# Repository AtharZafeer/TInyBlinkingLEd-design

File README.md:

# TInyBlinkingLEd-design
This contains the schematic and pcb design of a circuit that will blink every 1 seconds

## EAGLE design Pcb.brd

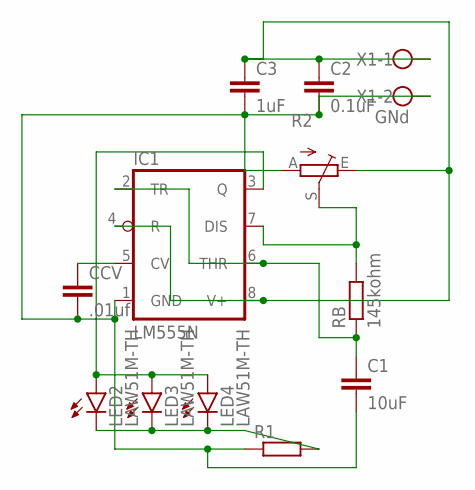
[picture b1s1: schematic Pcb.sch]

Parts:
C1: 10uF; C2.5-2
C2: 0.1uF; C025-024X044
C3: 1uF; C2.5-2
CCV: .01uf; C2.5-2
IC1: LM555N; DIL08
LED2, LED3, LED4: LAW51M-TH; W51-COOL
R1: R-EU_0309/12; 0309/12
R2: TRIM_EU-B25P; B25P
RB: 145kohm; 0309/12
X1: GNd; W237-102

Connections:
unnamed: C1.1, IC1.2 (TR), IC1.6 (THR), RB.1
unnamed: IC1.7 (DIS), R2.S, RB.2
unnamed: LED2.C, LED3.C, LED4.C, R1.2
unnamed: C1.2, C2.2, C3.2, CCV.2, IC1.1 (GND), R1.1, R2.A, X1.2
unnamed: CCV.1, IC1.5 (CV)
unnamed: C2.1, C3.1, IC1.4 (R), IC1.8 (V+), R2.E, X1.1
unnamed: IC1.3 (Q), LED2.A, LED3.A, LED4.A

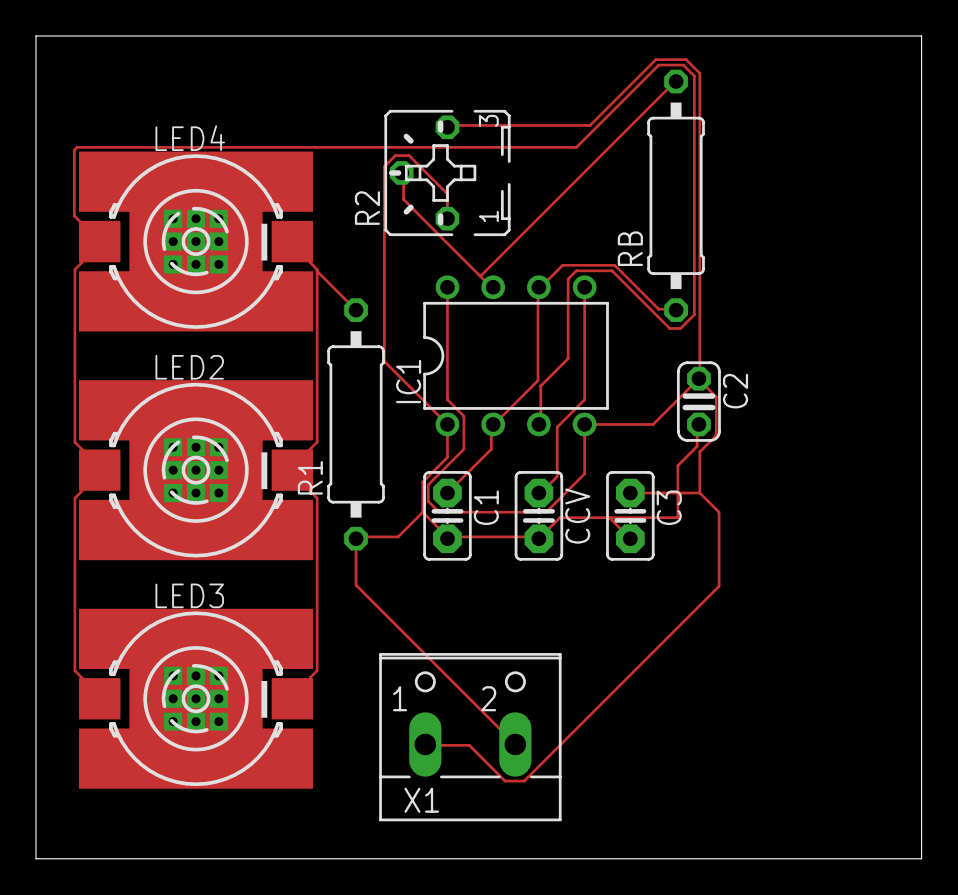
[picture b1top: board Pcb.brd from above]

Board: 2 copper layers, 49.2 x 45.7 mm, 12 parts (0 on the bottom side), 7 nets.
